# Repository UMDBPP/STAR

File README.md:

# STAR
Sratification and Tribocharging Analysis of Regolith

## Purpose
This is a payload for the 2017 RockSatX project. It's purpose is to provide experimental data for validating a behavioral model proposed by Dr. Christine Hartzell.

The payload will:
* Observe stratification of varying bimodal grain size distribution under microgravity and external excitation
* Measure effect of tribocharging upon spherical non-conducting grains

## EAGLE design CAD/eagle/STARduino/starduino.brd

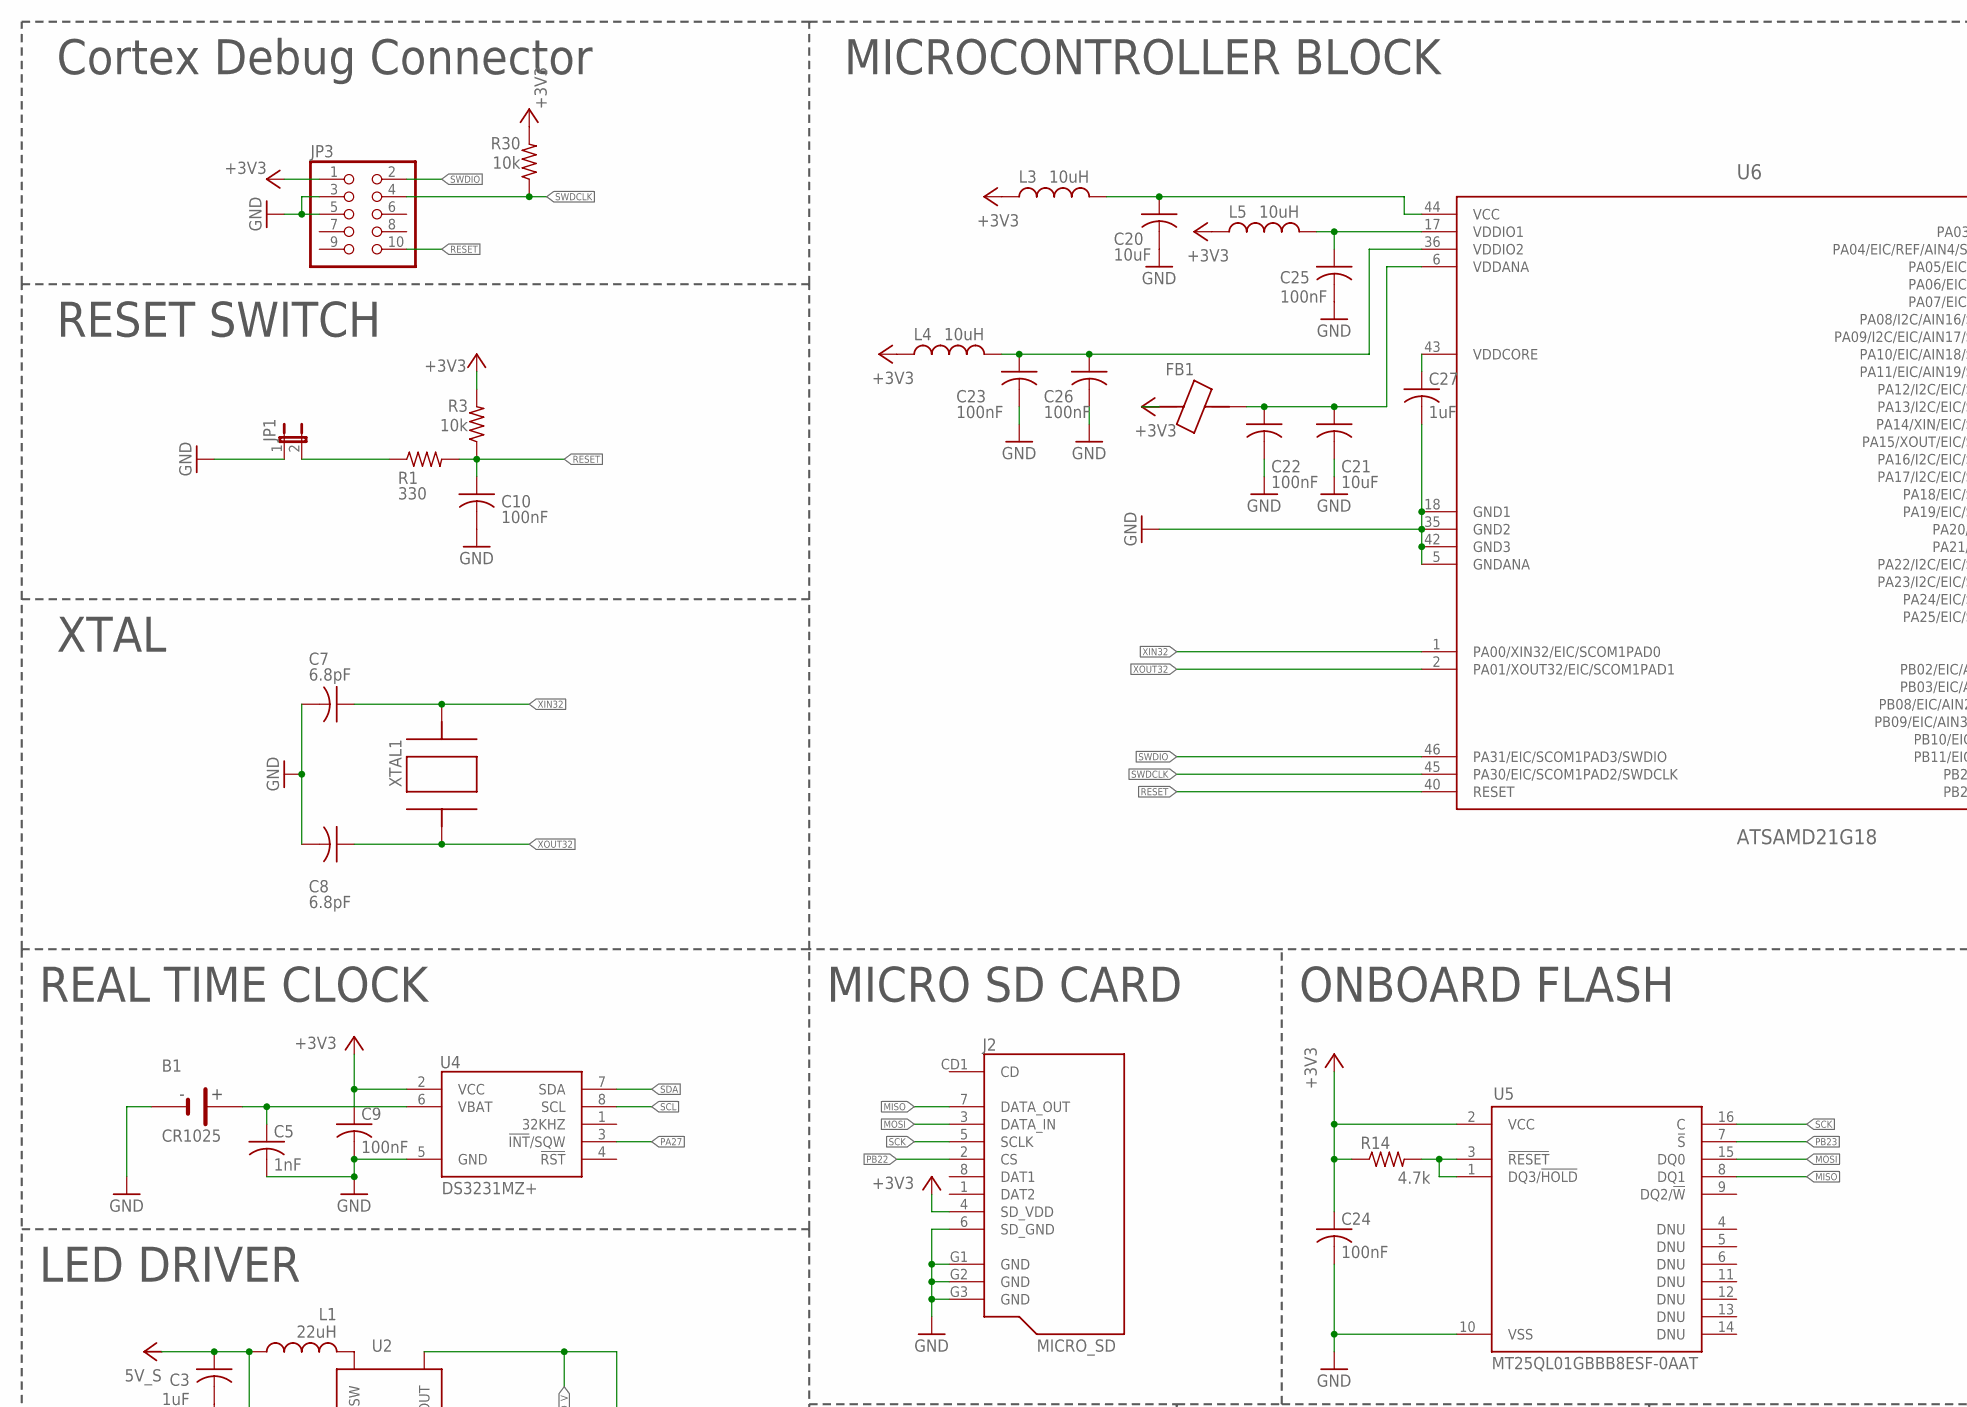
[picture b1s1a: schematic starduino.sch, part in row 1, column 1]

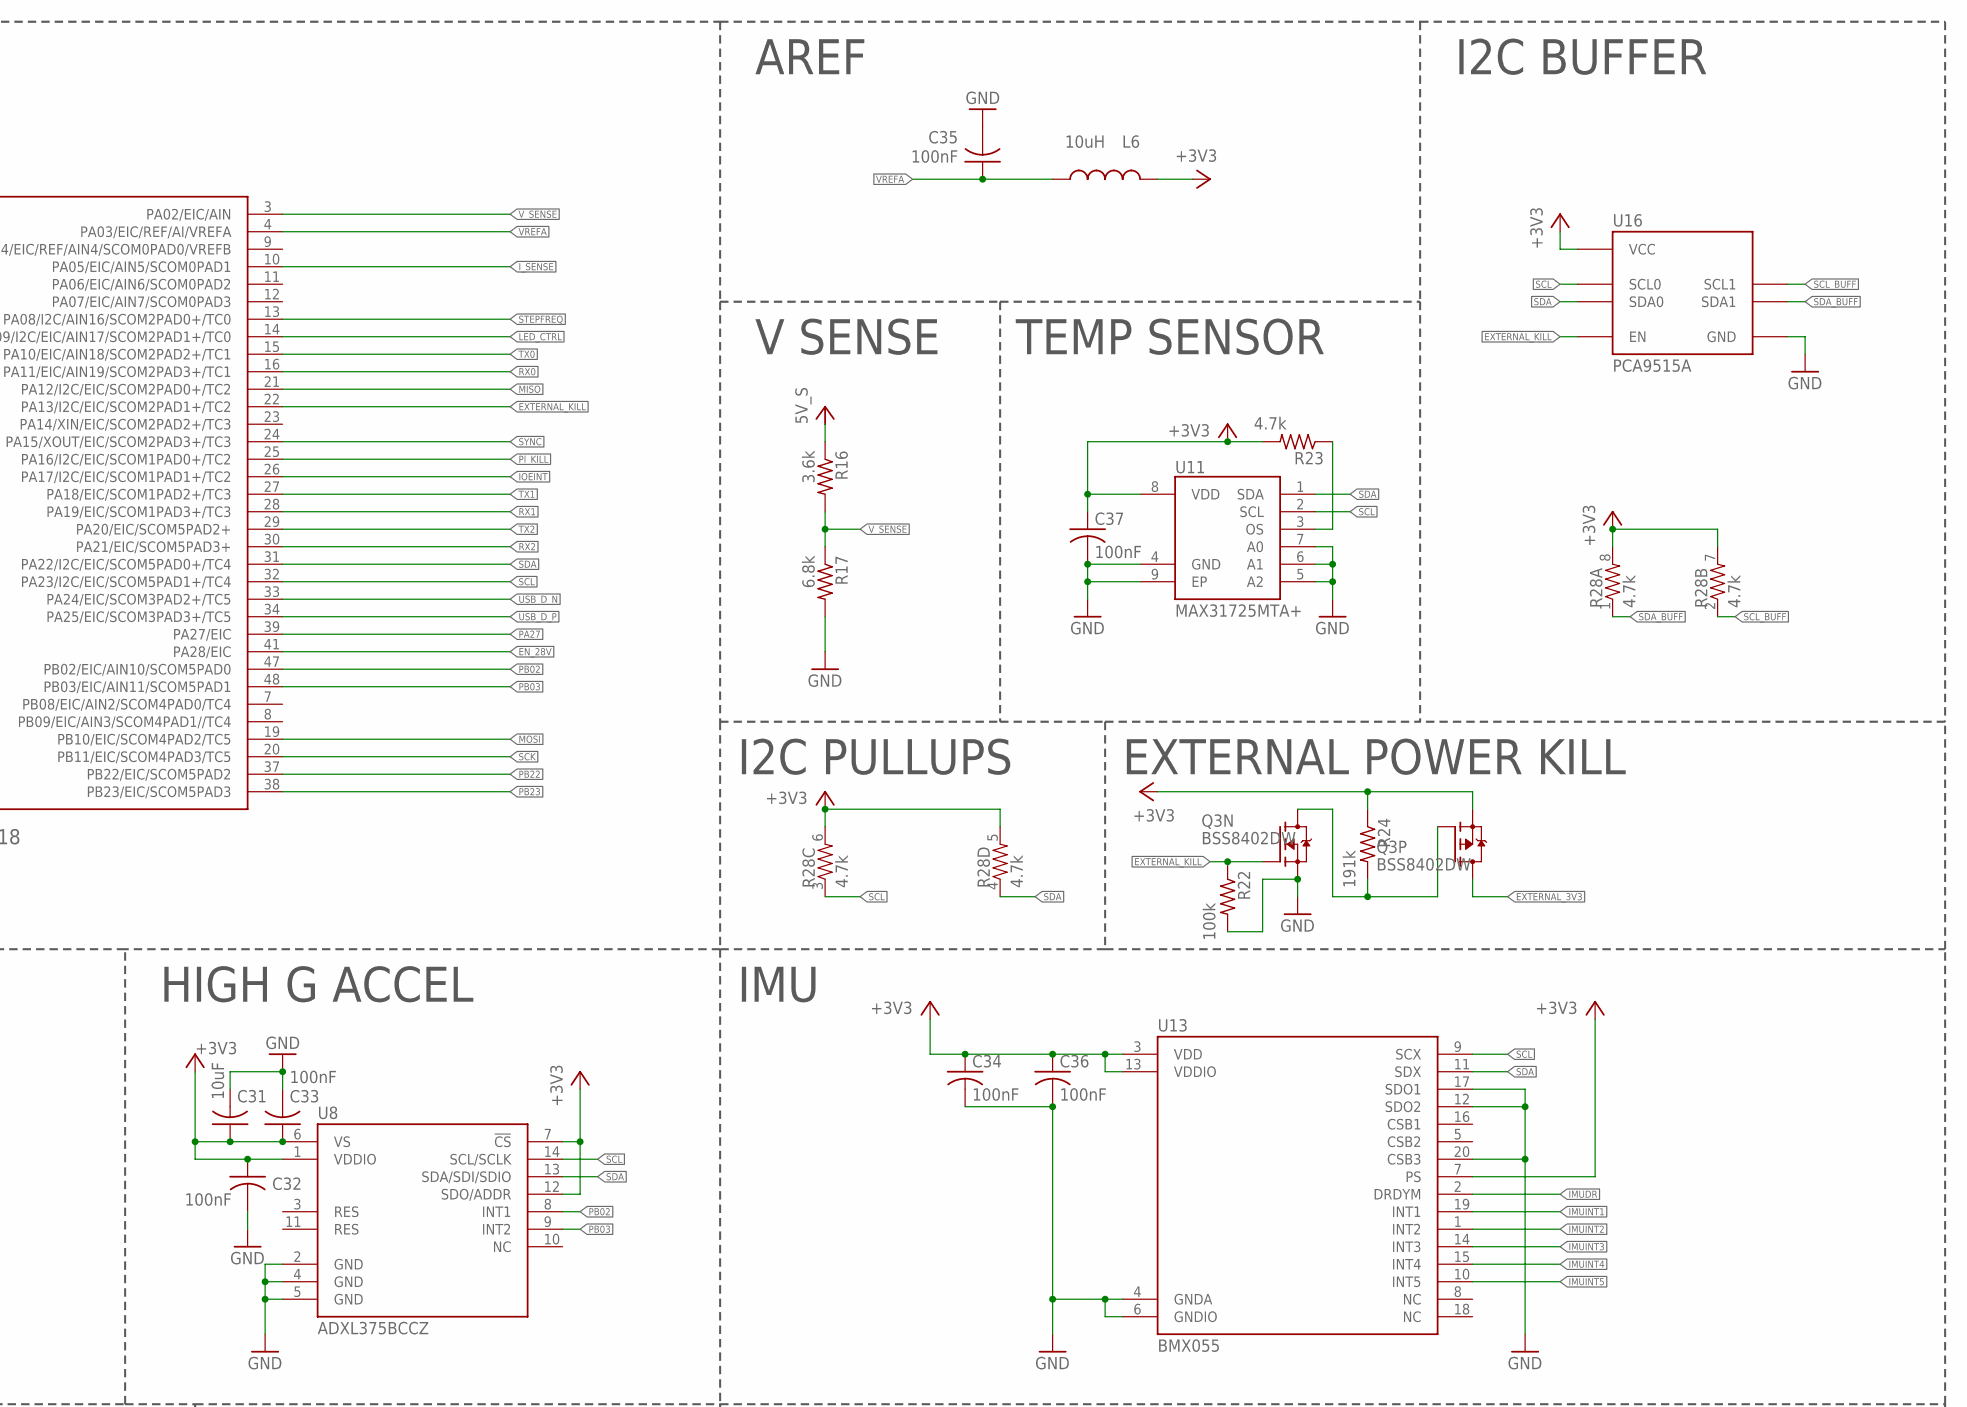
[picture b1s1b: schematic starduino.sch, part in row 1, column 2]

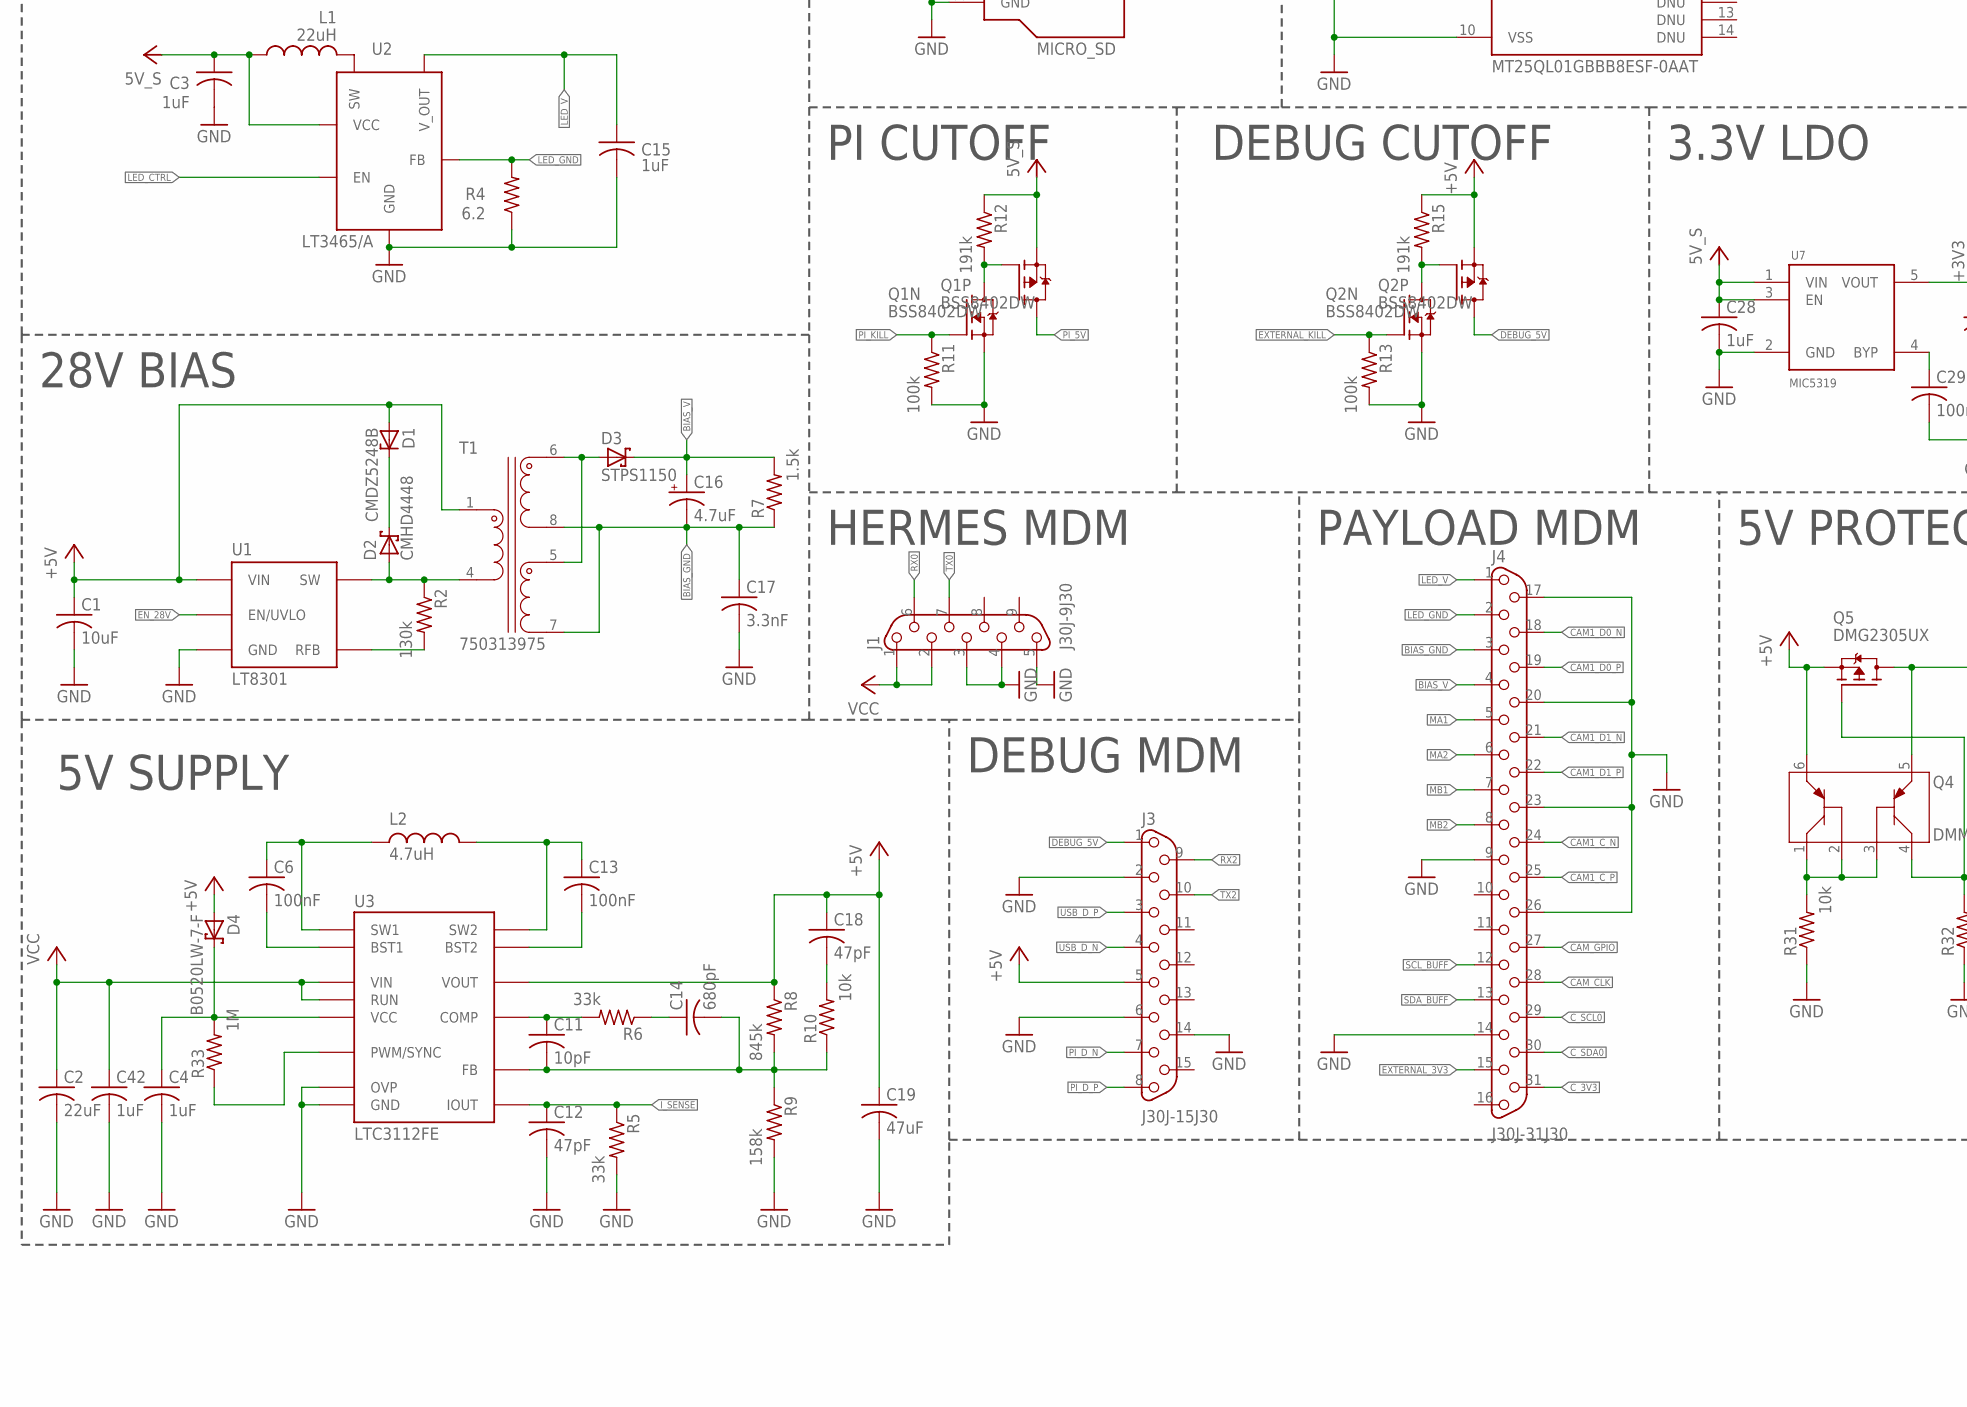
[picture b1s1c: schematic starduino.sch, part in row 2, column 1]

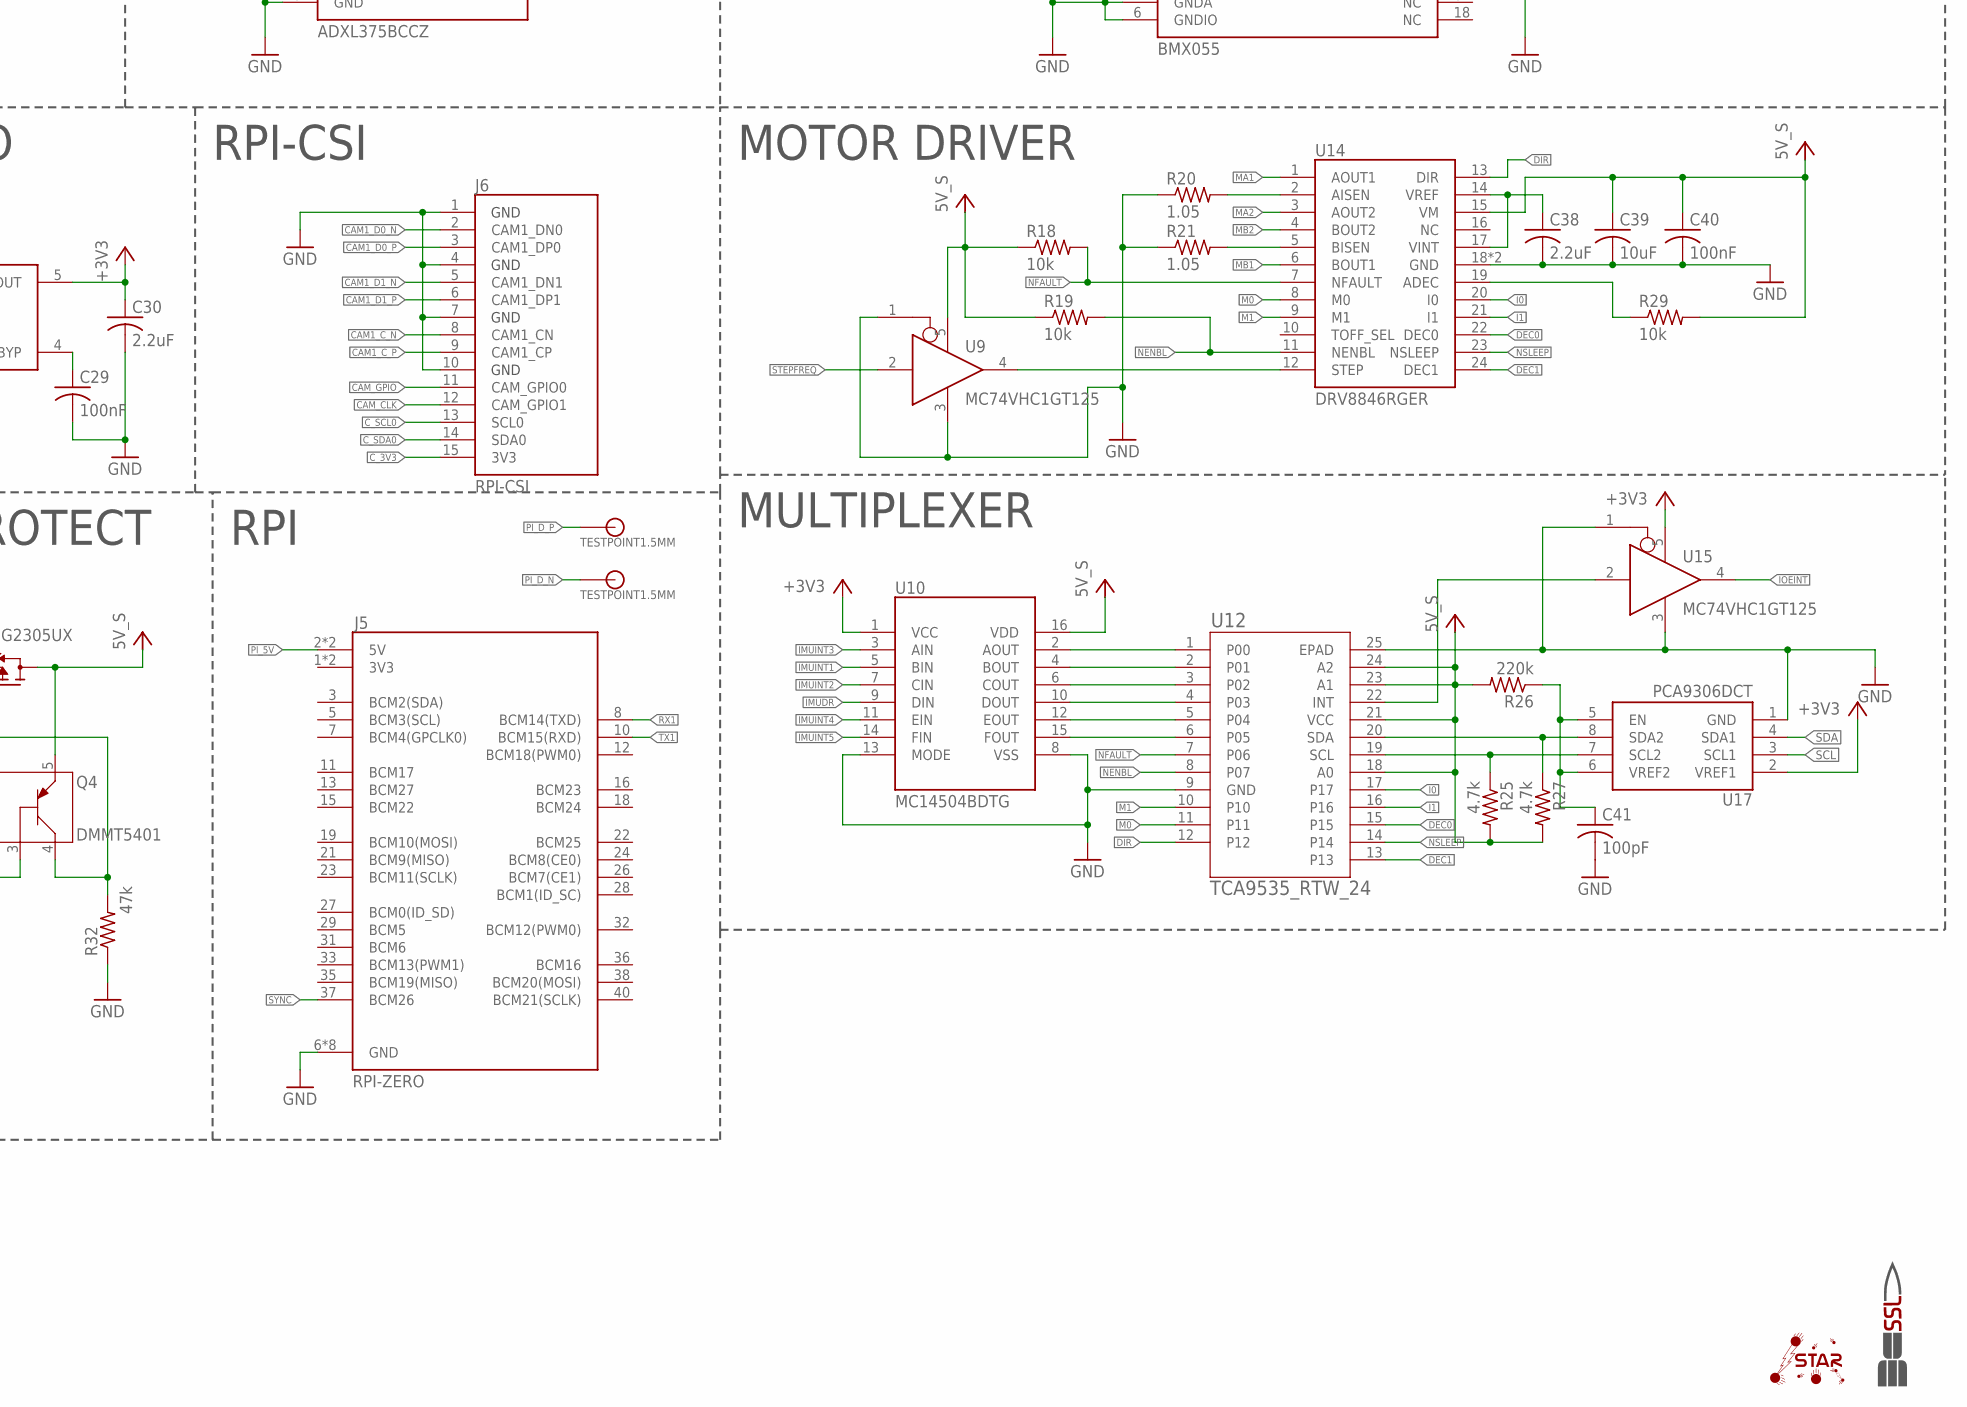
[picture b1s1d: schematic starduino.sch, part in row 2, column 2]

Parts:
B1: CR1025
C1: 10uF; C1206
C2: 22uF; C1206
C3, C4, C15, C27, C28, C42: 1uF; C0603
C5: 1nF; C0603
C6, C9, C10, C13, C22, C23, C24, C25, C26, C29, C32, C33, C34, C35, C36, C37, C40: 100nF; C0603
C7, C8: 6.8pF; C0603
C11: 10pF; C0603
C12, C18: 47pF; C0603
C14: 680pF; C0603
C16: 4.7uF; KEMET_B
C17: 3.3nF; C1206
C19: 47uF; C1210
C20, C21, C31, C39: 10uF; C0603
C30, C38: 2.2uF; C0603
C41: 100pF; C0603
D1: CMDZ5248B; SOD323-W
D2: CMHD4448; SOD123
D3: STPS1150; SMA
D4: B0520LW-7-F; SOD123
FB1: BLM18KG221BH1D; 0603
J1: J30J-9J30; ZKN-9-J30
J2: MICRO_SD; MICROSD_PUSH_PUSH_AMPHENOL
J3: J30J-15J30; ZKN-15-J30
J4: J30J-31J30; ZKN-31-J30
J5: RPI-ZERO; 2X20-OFFSET
J6: RPI-CSI; 1-1734248-5
JP1: JUMPER-2PTH; 1X02
JP3: PINHD-2X5; 2X5/90-50MIL
L1: 22uH; VLF504012MT(TDK)
L2: 4.7uH; SRP5030
L3, L4, L5, L6: 10uH; 0603
Q1, Q2, Q3: BSS8402DW; SC70
Q4: DMMT5401; SOT-26
Q5: DMG2305UX; SOT23
R1: 330; R0603
R2: 130k; R0603
R3, R10, R18, R19, R29, R30, R31: 10k; R0603
R4: 6.2; R0603
R5, R6: 33k; R0603
R7: 1.5k; R1206
R8: 845k; R0603
R9: 158k; R0603
R11, R13, R22: 100k; R0603
R12, R15, R24: 191k; R0603
R14, R23, R25, R27: 4.7k; R0603
R16: 3.6k; R0603
R17: 6.8k; R0603
R20, R21: 1.05; R0603
R26: 220k; R0603
R28: 4.7k; 0603-ARV
R32: 47k; R0603
R33: 1M; R0603
T1: 750313975; 750313972
TP1, TP2: TESTPOINT1.5MM; TP-1.5MM
U1: LT8301; SOT23-5L
U2: LT3465/A; SOT23-6
U3: LTC3112FE; TSSOP20
U4: DS3231MZ+; SOIC-8
U5: MT25QL01GBBB8ESF-0AAT; SOP2-16
U6: ATSAMD21G18; 48-TQFP
U7: MIC5319; SOT23-5L
U8: ADXL375BCCZ; LGA-14
U9, U15: MC74VHC1GT125; SC-70-5
U10: MC14504BDTG; TSSOP16
U11: MAX31725MTA+; DFN-8
U12: TCA9535_RTW_24; RTW24_2P45X2P45
U13: BMX055; LGA-20
U14: DRV8846RGER; VQFN6
U16: PCA9515A; TSSOP8
U17: PCA9306DCT; SSOP8
U$1: STAR; STAR_.3IN
U$2: SSL.3IN_SILK; SSL_SILK_.3IN
XTAL1: ABS07AIG-32.768KHZ-1-T; 2-SMD

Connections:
5V_S: C3.1, C28.1, C39.1, C40.1, L1.P$1 (1), Q1.4 (S), Q4.5 (E2), Q5.3 (D), R12.1, R16.1, R18.1, R19.1, R25.2, R26.2, R27.2, R29.2, U2.5 (VCC), U7.1 (VIN), U7.3 (EN), U9.5 (VIN), U10.16 (VDD), U12.18 (A0), U12.21 (VCC), U12.23 (A1), U12.24 (A2), U14.15 (VM)
+3V3: C9.1, C24.1, C30.1, C31.1, C32.1, C33.1, C34.1, C36.1, C37.1, FB1.1, J2.4 (SD_VDD), JP3.1, L3.1, L4.1, L5.1, L6.2, Q3.4 (S), R3.2, R14.1, R23.2, R24.1, R28.5 (2), R28.6 (2), R28.7 (2), R28.8 (2), R30.2, U4.2 (VCC), U5.2 (VCC), U7.5 (VOUT), U8.1 (VDDIO), U8.6 (VS), U8.7 (!CS!), U8.12 (SDO/ADDR), U10.1 (VCC), U11.8 (VDD), U13.3 (VDD), U13.7 (PS), U13.13 (VDDIO), U15.5 (VIN), U16.P$8 (VCC), U17.2 (VREF1)
+5V: C1.1, C18.1, C19.1, D1.A, D4.A, J3.5, Q2.4 (S), Q4.6 (E1), Q5.2 (S), R8.1, R15.1, T1.1, U1.5 (VIN), U3.9 (VOUT)
BIAS_GND: C16.N (-), C17.1, J4.3, R7.1, T1.7, T1.8
BIAS_V: C16.P (+), D3.C, J4.4, R7.2
CAM1_C_N: J4.24, J6.8 (CAM1_CN)
CAM1_C_P: J4.25, J6.9 (CAM1_CP)
CAM1_D0_N: J4.18, J6.2 (CAM1_DN0)
CAM1_D0_P: J4.19, J6.3 (CAM1_DP0)
CAM1_D1_N: J4.21, J6.5 (CAM1_DN1)
CAM1_D1_P: J4.22, J6.6 (CAM1_DP1)
CAM_CLK: J4.28, J6.12 (CAM_GPIO1)
CAM_GPIO: J4.27, J6.11 (CAM_GPIO0)
C_3V3: J4.31, J6.15 (3V3)
C_SCL0: J4.29, J6.13 (SCL0)
C_SDA0: J4.30, J6.14 (SDA0)
DEBUG_5V: J3.1, Q2.3 (D)
DEC0: U12.15, U14.22 (DEC0)
DEC1: U12.13, U14.24 (DEC1)
DIR: U12.12, U14.13 (DIR)
EN_28V: U1.1 (EN/UVLO), U6.41 (PA28/EIC)
EXTERNAL_3V3: J4.15, Q3.3 (D)
EXTERNAL_KILL: Q2.2 (G), Q3.2 (G), R13.1, R22.1, U6.22 (PA13/I2C/EIC/SCOM2PAD1+/TC2), U16.P$5 (EN)
FB_5: C11.2, C14.2, R8.2, R9.1, R10.1, U3.3 (FB)
GND: B1.3 (-), C1.2, C2.2, C3.2, C4.2, C5.2, C7.2, C8.2, C9.2, C10.2, C12.2, C15.2, C17.2, C19.2, C20.2, C21.2, C22.2, C23.2, C24.2, C25.2, C26.2, C27.2, C28.2, C29.2, C30.2, C31.2, C32.2, C33.2, C34.2, C35.2, C36.2, C37.2, C38.2, C39.2, C40.2, C41.2, C42.2, J1.3, J1.4, J1.5, J2.6 (SD_GND), J2.G1 (GND), J2.G2 (GND), J2.G3 (GND), J3.2, J3.6, J3.14, J4.9, J4.14, J4.17, J4.20, J4.23, J4.26, J5.6 (GND), J5.9 (GND), J5.14 (GND), J5.20 (GND), J5.25 (GND), J5.30 (GND), J5.34 (GND), J5.39 (GND), J6.1 (GND1), J6.4 (GND2), J6.7 (GND3), J6.10 (GND4), JP1.1, JP3.3, JP3.5, Q1.1 (S), Q2.1 (S), Q3.1 (S), R4.1, R5.2, R9.2, R11.2, R13.2, R17.2, R20.1, R21.1, R22.2, R31.1, R32.1, U1.2 (GND), U2.2 (GND), U3.1 (GND), U3.4 (OVP), U3.10 (GND), U3.11 (GND), U3.20 (GND), U3.PAD (GND), U4.5 (GND), U5.10 (VSS), U6.5 (GNDANA), U6.18 (GND1), U6.35 (GND2), U6.42 (GND3), U7.2 (GND), U8.2 (GND), U8.4 (GND), U8.5 (GND), U9.1 (OE), U9.3 (GND), U10.8 (VSS), U10.13 (MODE), U11.4 (GND), U11.5 (A2), U11.6 (A1), U11.7 (A0), U11.9 (EP), U12.9 (GND), U12.25 (EPAD), U13.4 (GNDA), U13.6 (GNDIO), U13.12 (SDO2), U13.17 (SDO1), U13.20 (CSB3), U14.18 (GND), U14.PPAD (GND), U15.1 (OE), U15.3 (GND), U16.P$4 (GND), U17.1 (GND)
I0: U12.17, U14.20 (I0)
I1: U12.16, U14.21 (I1)
IMUDR: U10.9 (DIN), U13.2 (DRDYM)
IMUINT1: U10.5 (BIN), U13.19 (INT1)
IMUINT2: U10.7 (CIN), U13.1 (INT2)
IMUINT3: U10.3 (AIN), U13.14 (INT3)
IMUINT4: U10.11 (EIN), U13.15 (INT4)
IMUINT5: U10.14 (FIN), U13.10 (INT5)
IOEINT: U6.26 (PA17/I2C/EIC/SCOM1PAD1+/TC2), U15.4 (Y)
I_SENSE: C12.1, R5.1, U3.8 (IOUT), U6.10 (PA05/EIC/AIN5/SCOM0PAD1)
LED_CTRL: U2.4 (EN), U6.14 (PA09/I2C/EIC/AIN17/SCOM2PAD1+/TC0)
LED_GND: J4.2, R4.2, U2.3 (FB)
LED_V: C15.1, J4.1, U2.1 (V_OUT)
M0: U12.11, U14.8 (M0)
M1: U12.10, U14.9 (M1)
MA1: J4.5, U14.1 (AOUT1)
MA2: J4.6, U14.3 (AOUT2)
MB1: J4.7, U14.6 (BOUT1)
MB2: J4.8, U14.4 (BOUT2)
MISO: J2.7 (DATA_OUT), U5.8 (DQ1), U6.21 (PA12/I2C/EIC/SCOM2PAD0+/TC2)
MOSI: J2.3 (DATA_IN), U5.15 (DQ0), U6.19 (PB10/EIC/SCOM4PAD2/TC5)
unnamed: Q4.4 (C2), Q5.1 (G), R32.2
unnamed: Q4.1 (C1), Q4.2 (B1), Q4.3 (B2), R31.2
unnamed: R33.1, U3.19 (PWM/SYNC)
unnamed: C25.1, L5.2, U6.17 (VDDIO1)
unnamed: C27.1, U6.43 (VDDCORE)
unnamed: R23.1, U11.3 (OS)
unnamed: JP1.2, R1.1
unnamed: B1.1 (+), B1.2 (+), C5.1, U4.6 (VBAT)
unnamed: C29.1, U7.4 (BYP)
unnamed: C21.1, C22.1, FB1.2, U6.6 (VDDANA)
unnamed: C14.1, R6.1
unnamed: C11.1, R6.2, U3.2 (COMP)
unnamed: C20.1, L3.2, U6.44 (VCC)
unnamed: L1.P$2 (2), U2.6 (SW)
unnamed: R29.1, U14.19 (ADEC)
unnamed: Q3.5 (G), Q3.6 (D), R24.2
unnamed: U10.2 (AOUT), U12.1 (P00)
unnamed: R21.2, U14.5 (BISEN)
unnamed: R20.2, U14.2 (AISEN)
unnamed: U9.4 (Y), U14.12 (STEP)
unnamed: U10.4 (BOUT), U12.2 (P01)
unnamed: C23.1, C26.1, L4.2, U6.36 (VDDIO2)
unnamed: U12.22 (INT), U15.2 (A)
unnamed: C38.1, U14.14 (VREF), U14.17 (VINT)
unnamed: U10.6 (COUT), U12.3 (P02)
unnamed: U10.10 (DOUT), U12.4 (P03)
unnamed: U10.12 (EOUT), U12.5 (P04)
unnamed: U10.15 (FOUT), U12.6 (P05)
unnamed: R14.2, U5.1 (DQ3/!HOLD!), U5.3 (!RESET!)
unnamed: R27.1, U12.20 (SDA), U17.8 (SDA2)
unnamed: R25.1, U12.19 (SCL), U17.7 (SCL2)
unnamed: C41.1, R26.1, U17.5 (EN), U17.6 (VREF2)
unnamed: Q1.5 (G), Q1.6 (D), R12.2
unnamed: Q2.5 (G), Q2.6 (D), R15.2
unnamed: C6.1, L2.P$1, U3.15 (SW1), U3.16 (SW1)
unnamed: C13.1, L2.P$2, U3.12 (SW2), U3.13 (SW2)
unnamed: C6.2, U3.17 (BST1)
unnamed: C13.2, U3.14 (BST2)
unnamed: C4.1, D4.C, R33.2, U3.18 (VCC)
unnamed: C18.2, R10.2
unnamed: R2.2, U1.3 (RFB)
unnamed: D2.A, R2.1, T1.4, U1.4 (SW)
unnamed: D1.C, D2.C
unnamed: D3.A, T1.5, T1.6
NENBL: R19.2, U12.8 (P07), U14.11 (NENBL)
NFAULT: R18.2, U12.7 (P06), U14.7 (NFAULT)
NSLEEP: U12.14, U14.23 (NSLEEP)
PA27: U4.3 (!INT!/SQW), U6.39 (PA27/EIC)
PB02: U6.47 (PB02/EIC/AIN10/SCOM5PAD0), U8.8 (INT1)
PB03: U6.48 (PB03/EIC/AIN11/SCOM5PAD1), U8.9 (INT2)
PB22: J2.2 (CS), U6.37 (PB22/EIC/SCOM5PAD2)
PB23: U5.7 (!S!), U6.38 (PB23/EIC/SCOM5PAD3)
PI_5V: J5.2 (5V), J5.4 (5V), Q1.3 (D)
PI_D_N: J3.7, TP2.P$1
PI_D_P: J3.8, TP1.P$1
PI_KILL: Q1.2 (G), R11.1, U6.25 (PA16/I2C/EIC/SCOM1PAD0+/TC2)
RESET: C10.1, JP3.10, R1.2, R3.1, U6.40 (RESET)
RX0: J1.6, U6.16 (PA11/EIC/AIN19/SCOM2PAD3+/TC1)
RX1: J5.8 (BCM14(TXD)), U6.28 (PA19/EIC/SCOM1PAD3+/TC3)
RX2: J3.9, U6.30 (PA21/EIC/SCOM5PAD3+)
SCK: J2.5 (SCLK), U5.16 (C), U6.20 (PB11/EIC/SCOM4PAD3/TC5)
SCL: R28.3 (1), U4.8 (SCL), U6.32 (PA23/I2C/EIC/SCOM5PAD1+/TC4), U8.14 (SCL/SCLK), U11.2 (SCL), U13.9 (SCX), U16.P$2 (SCL0), U17.3 (SCL1)
SCL_BUFF: J4.12, R28.2 (1), U16.P$7 (SCL1)
SDA: R28.4 (1), U4.7 (SDA), U6.31 (PA22/I2C/EIC/SCOM5PAD0+/TC4), U8.13 (SDA/SDI/SDIO), U11.1 (SDA), U13.11 (SDX), U16.P$3 (SDA0), U17.4 (SDA1)
SDA_BUFF: J4.13, R28.1, U16.P$6 (SDA1)
STEPFREQ: U6.13 (PA08/I2C/AIN16/SCOM2PAD0+/TC0), U9.2 (A)
SWDCLK: JP3.4, R30.1, U6.45 (PA30/EIC/SCOM1PAD2/SWDCLK)
SWDIO: JP3.2, U6.46 (PA31/EIC/SCOM1PAD3/SWDIO)
SYNC: J5.37 (BCM26), U6.24 (PA15/XOUT/EIC/SCOM2PAD3+/TC3)
TX0: J1.7, U6.15 (PA10/EIC/AIN18/SCOM2PAD2+/TC1)
TX1: J5.10 (BCM15(RXD)), U6.27 (PA18/EIC/SCOM1PAD2+/TC3)
TX2: J3.10, U6.29 (PA20/EIC/SCOM5PAD2+)
USB_D_N: J3.4, U6.33 (PA24/EIC/SCOM3PAD2+/TC5)
USB_D_P: J3.3, U6.34 (PA25/EIC/SCOM3PAD3+/TC5)
VCC: C2.1, C42.1, J1.1, J1.2, U3.5 (VIN), U3.6 (VIN), U3.7 (RUN)
VREFA: C35.1, L6.1, U6.4 (PA03/EIC/REF/AI/VREFA)
V_SENSE: R16.2, R17.1, U6.3 (PA02/EIC/AIN)
XIN32: C7.1, U6.1 (PA00/XIN32/EIC/SCOM1PAD0), XTAL1.P2 (2)
XOUT32: C8.1, U6.2 (PA01/XOUT32/EIC/SCOM1PAD1), XTAL1.P1 (1)

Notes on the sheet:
MICROCONTROLLER BLOCK
Cortex Debug Connector
RESET SWITCH
XTAL
AREF
V SENSE
I2C PULLUPS
HIGH G ACCEL
TEMP SENSOR
REAL TIME CLOCK
IMU
MICRO SD CARD
ONBOARD FLASH
LED DRIVER
MOTOR DRIVER
MULTIPLEXER
PI CUTOFF
DEBUG CUTOFF
I2C BUFFER
EXTERNAL POWER KILL
28V BIAS
3.3V LDO
5V SUPPLY
HERMES MDM
DEBUG MDM
PAYLOAD MDM
RPI-CSI
RPI
5V PROTECT

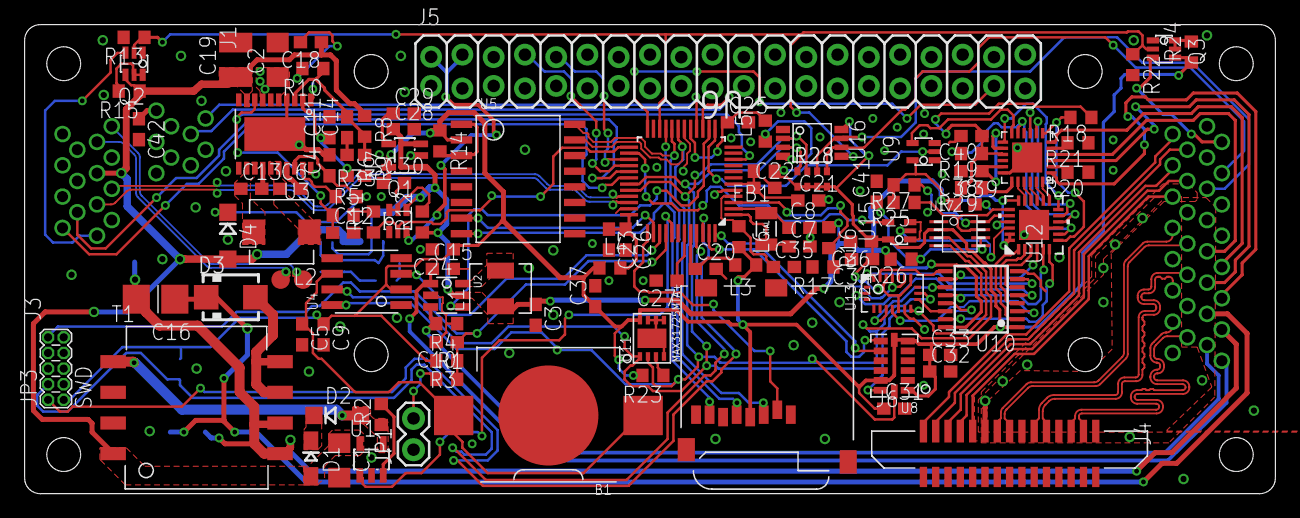
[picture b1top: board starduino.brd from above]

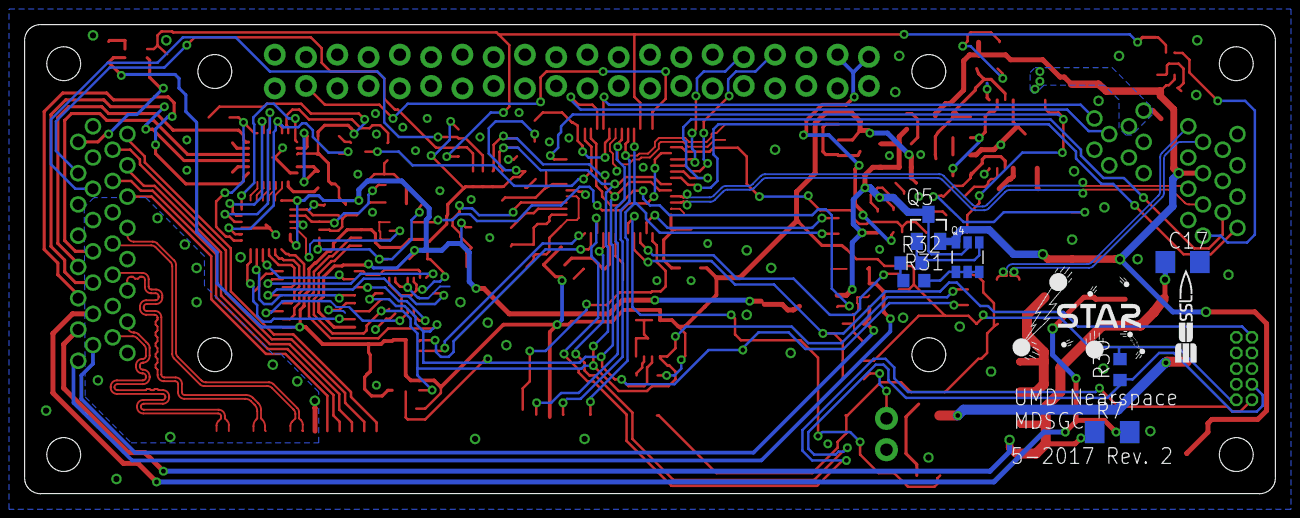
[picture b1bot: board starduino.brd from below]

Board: 2 copper layers, 101.6 x 38.1 mm, 123 parts (9 on the bottom side), 125 nets.

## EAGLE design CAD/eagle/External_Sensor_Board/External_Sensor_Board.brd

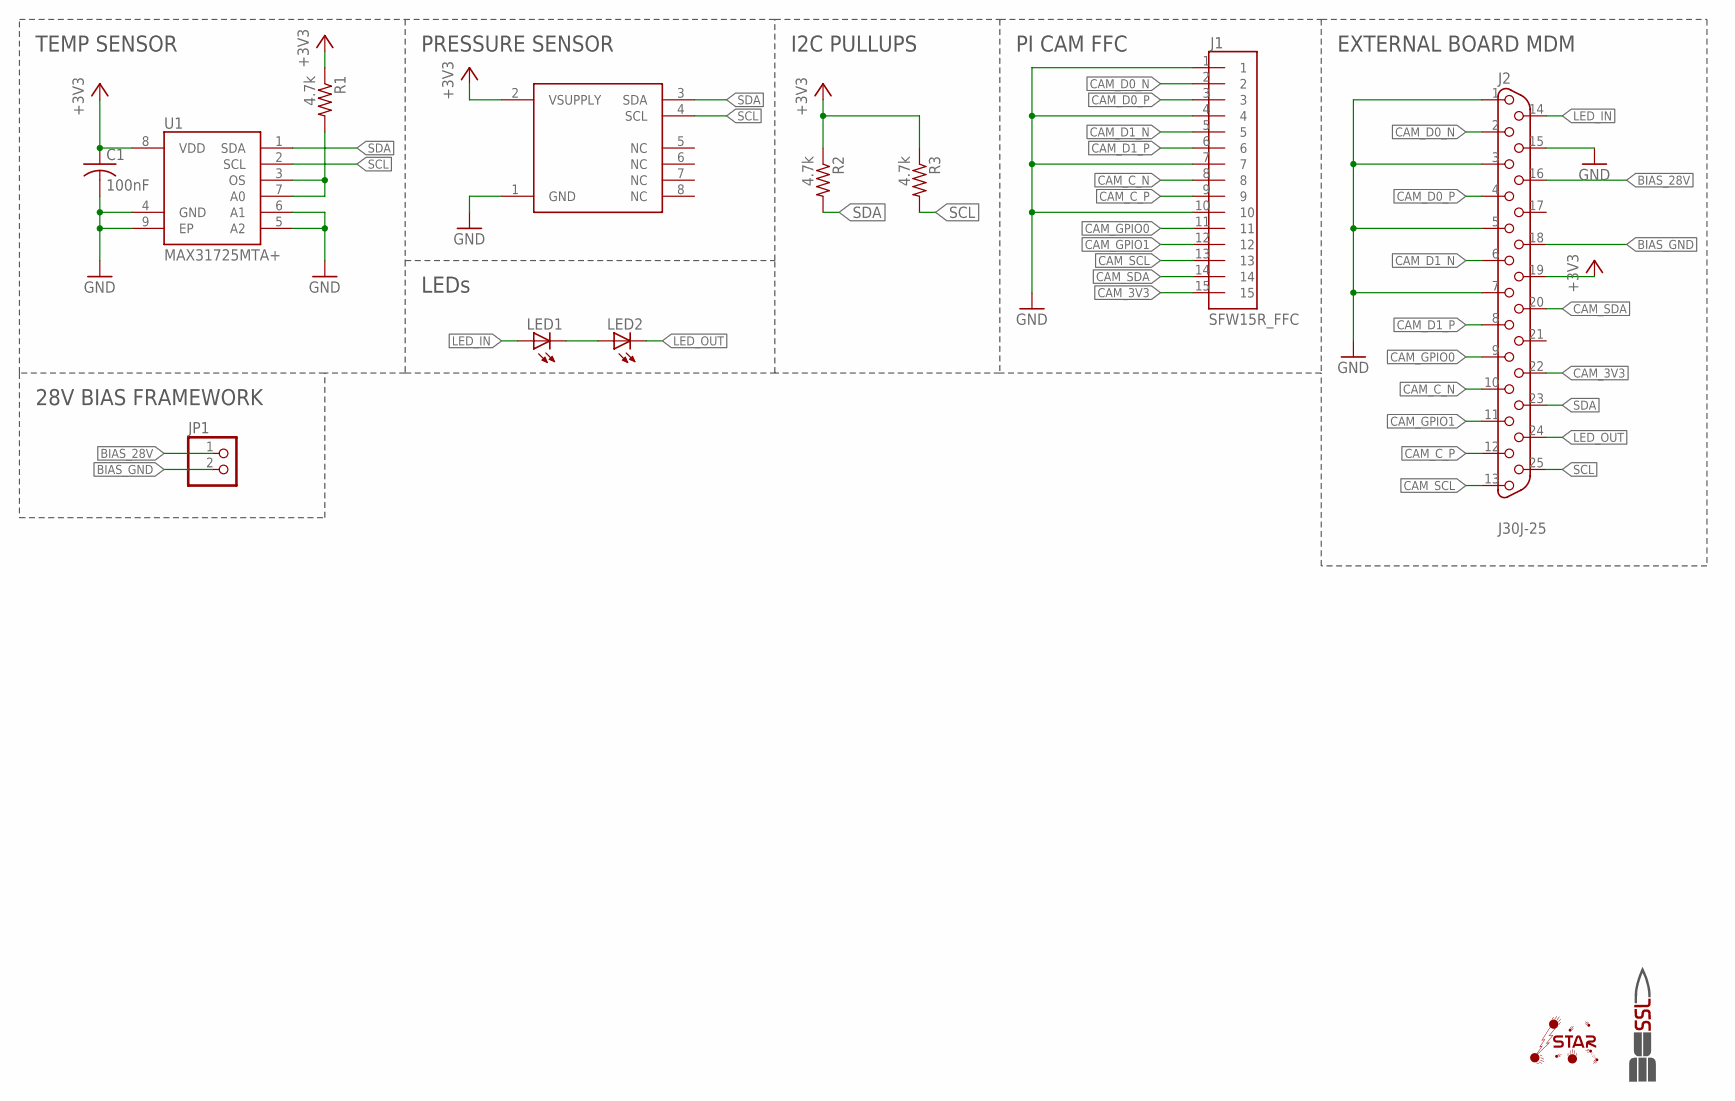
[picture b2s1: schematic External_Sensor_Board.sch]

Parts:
C1: 100nF; C0603
J1: SFW15R_FFC; AMPHENOL_15_FFC
J2: J30J-25; ZKN-25
JP1: PINHD-1X2; 1X02
LED1, LED2: LED_1206_NS; 1206_NS
R1, R2, R3: 4.7k; R0603
U1: MAX31725MTA+; DFN-8
U2: SSCMNNN015PA2A3; HSC-SMT-8
U$1: SSL.3IN_SILK; SSL_SILK_.3IN
U$2: STAR; STAR_.3IN

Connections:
+3V3: C1.1, J2.19, R1.1, R2.1, R3.1, U1.8 (VDD), U2.2 (VSUPPLY)
BIAS_28V: J2.16, JP1.1
BIAS_GND: J2.18, JP1.2
CAM_3V3: J1.15, J2.22
CAM_C_N: J1.8, J2.10
CAM_C_P: J1.9, J2.12
CAM_D0_N: J1.2, J2.2
CAM_D0_P: J1.3, J2.4
CAM_D1_N: J1.5, J2.6
CAM_D1_P: J1.6, J2.8
CAM_GPIO0: J1.11, J2.9
CAM_GPIO1: J1.12, J2.11
CAM_SCL: J1.13, J2.13
CAM_SDA: J1.14, J2.20
GND: C1.2, J1.1, J1.4, J1.7, J1.10, J2.1, J2.3, J2.5, J2.7, J2.15, U1.4 (GND), U1.5 (A2), U1.6 (A1), U1.9 (EP), U2.1 (GND)
LED_IN: J2.14, LED1.2 (A)
LED_OUT: J2.24, LED2.1 (C)
unnamed: R1.2, U1.3 (OS), U1.7 (A0)
unnamed: LED1.1 (C), LED2.2 (A)
SCL: J2.25, R3.2, U1.2 (SCL), U2.4 (SCL)
SDA: J2.23, R2.2, U1.1 (SDA), U2.3 (SDA)

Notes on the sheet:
TEMP SENSOR
PRESSURE SENSOR
I2C PULLUPS
PI CAM FFC
EXTERNAL BOARD MDM
LEDs
28V BIAS FRAMEWORK

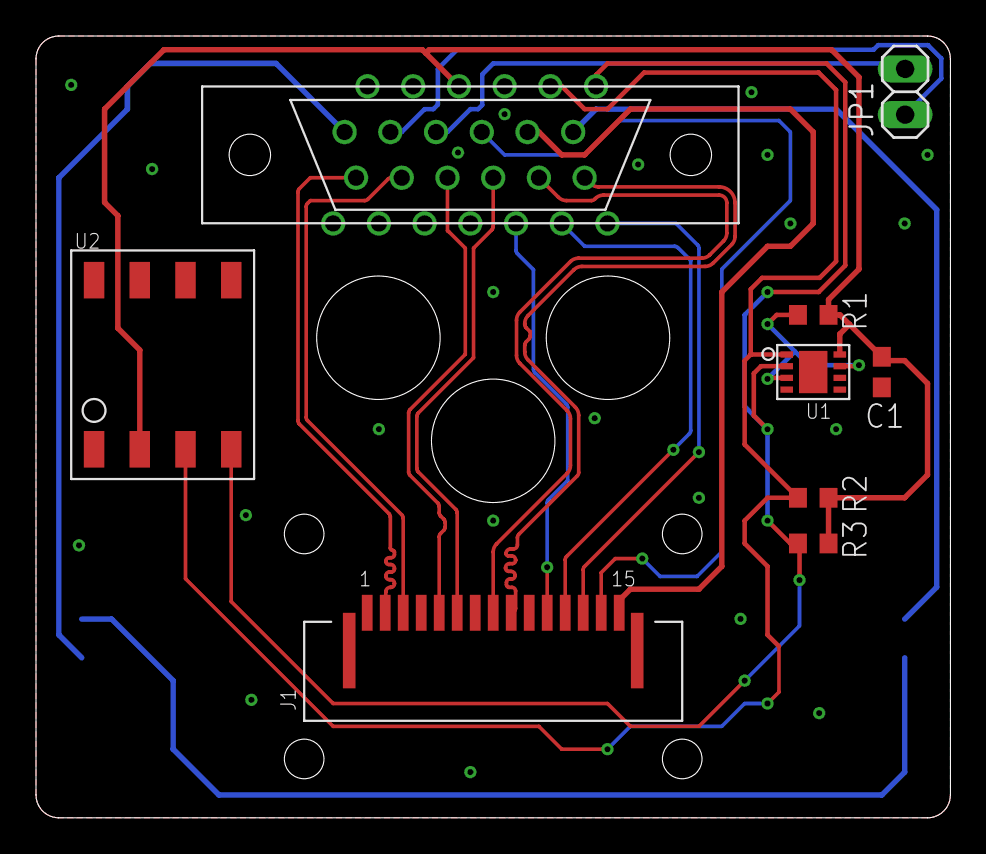
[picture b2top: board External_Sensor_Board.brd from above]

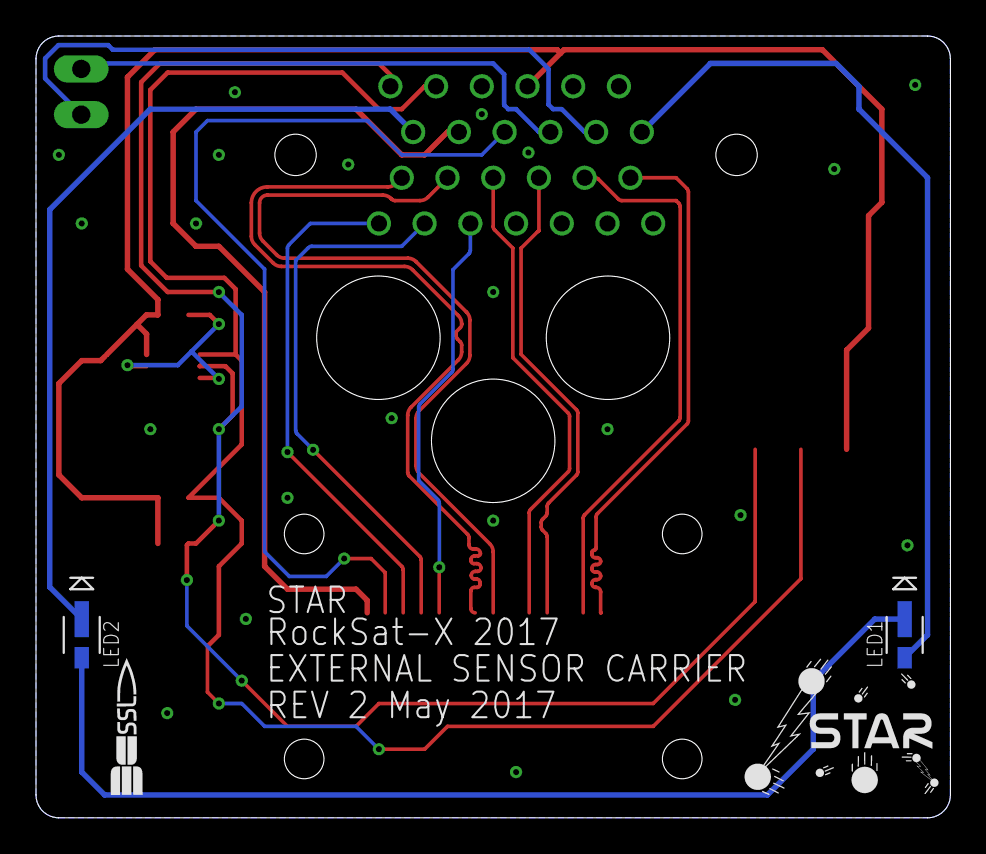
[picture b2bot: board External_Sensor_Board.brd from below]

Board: 2 copper layers, 50.8 x 43.4 mm, 13 parts (4 on the bottom side), 21 nets.

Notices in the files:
parts and their libraries:
SparkFun-Passives: Licensing: CC v3.0 Share-Alike You are welcome to use this library for commercial purposes.
